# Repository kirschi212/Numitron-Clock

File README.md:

# Numitron Clock by Kirschi

This is a small documentation if you want to build a Numitron Clock by yourself. This project is build around IV-9 tubes, an ESP8266 and the MAX7315 IO-Expander.

## Images

## Functioning

The ESP8266 is connected to the WiFi and retrieves the current time from a time server. The MAX7315 IO expanders are then controlled by the ESP8266 via I2C and switch the corresponding segments of the Numitron segments.
Optionally, a switch can also be installed with which the tubes can be switched off.

------

## Parts list

### Main Components:

Component  | Quantity | Description |
------------- | ------------- | ------------- |
ESP8266 NodeMCU  | 1 | heart of the circuit |
IV-9 numitron tubes | 4 | retro 7 segment displays |
MAX7315AEE+ | 4 | 8-bit IO-Expanders |
Custom PCB | 1 | Eagle.CAD files are uploaded in this repository |

### Other Components:

| Component  | Quantity | Description |
| ------------- | ------------- | ------------- | 
| Resistor 0603 47Ω  | 32  | current limiting resistors for numitron segments |
| Resistor 0603 4.7kΩ  | 2  | pull-up resistors for I2C-Bus |
| Ceramic capacitors  0603 0.047µF  | 4  | decoupling capacitors for MAX7315 |
| USB-C panel jack  | 1  | used for power supply via USB-C |
                    
### Optional Components:
These components can optionally be installed.

| Component  | Quantity | Description |
| ------------- | ------------- | ------------- |
| Resistor 0603 10kΩ  | 1 | pull-up resistor for switch |
| Electrolytic capacitor 100µF   | 1  | capacitor for voltage stabilization |
| Mechanical switch  | 1  | used for turning all segments on or off |

##### Notice: Either the electrolytic capacitor OR switch can be installed with this version of the PCB-design.

## PCB: schematic and board

#### Notice: This current version of the PCB shows some minor mistakes, e.g. the electrolytic capacitor can only be placed without installing a switch. Nevertheless the board is fully functional! If you are interested, I could design a second version of this board and I will try to improve it!

## Casing

In the repository you can find the Fusion360 file to the casing that I designed myself. It features mounting holes for the PCB, cutouts for the USB-C panel jack and the switch. You can print it with a common 3D-printer using PLA or PETG.

------
## Code

The code was designed to be uploaded to the ESP8266 via the Arduino IDE and a USB-connection.

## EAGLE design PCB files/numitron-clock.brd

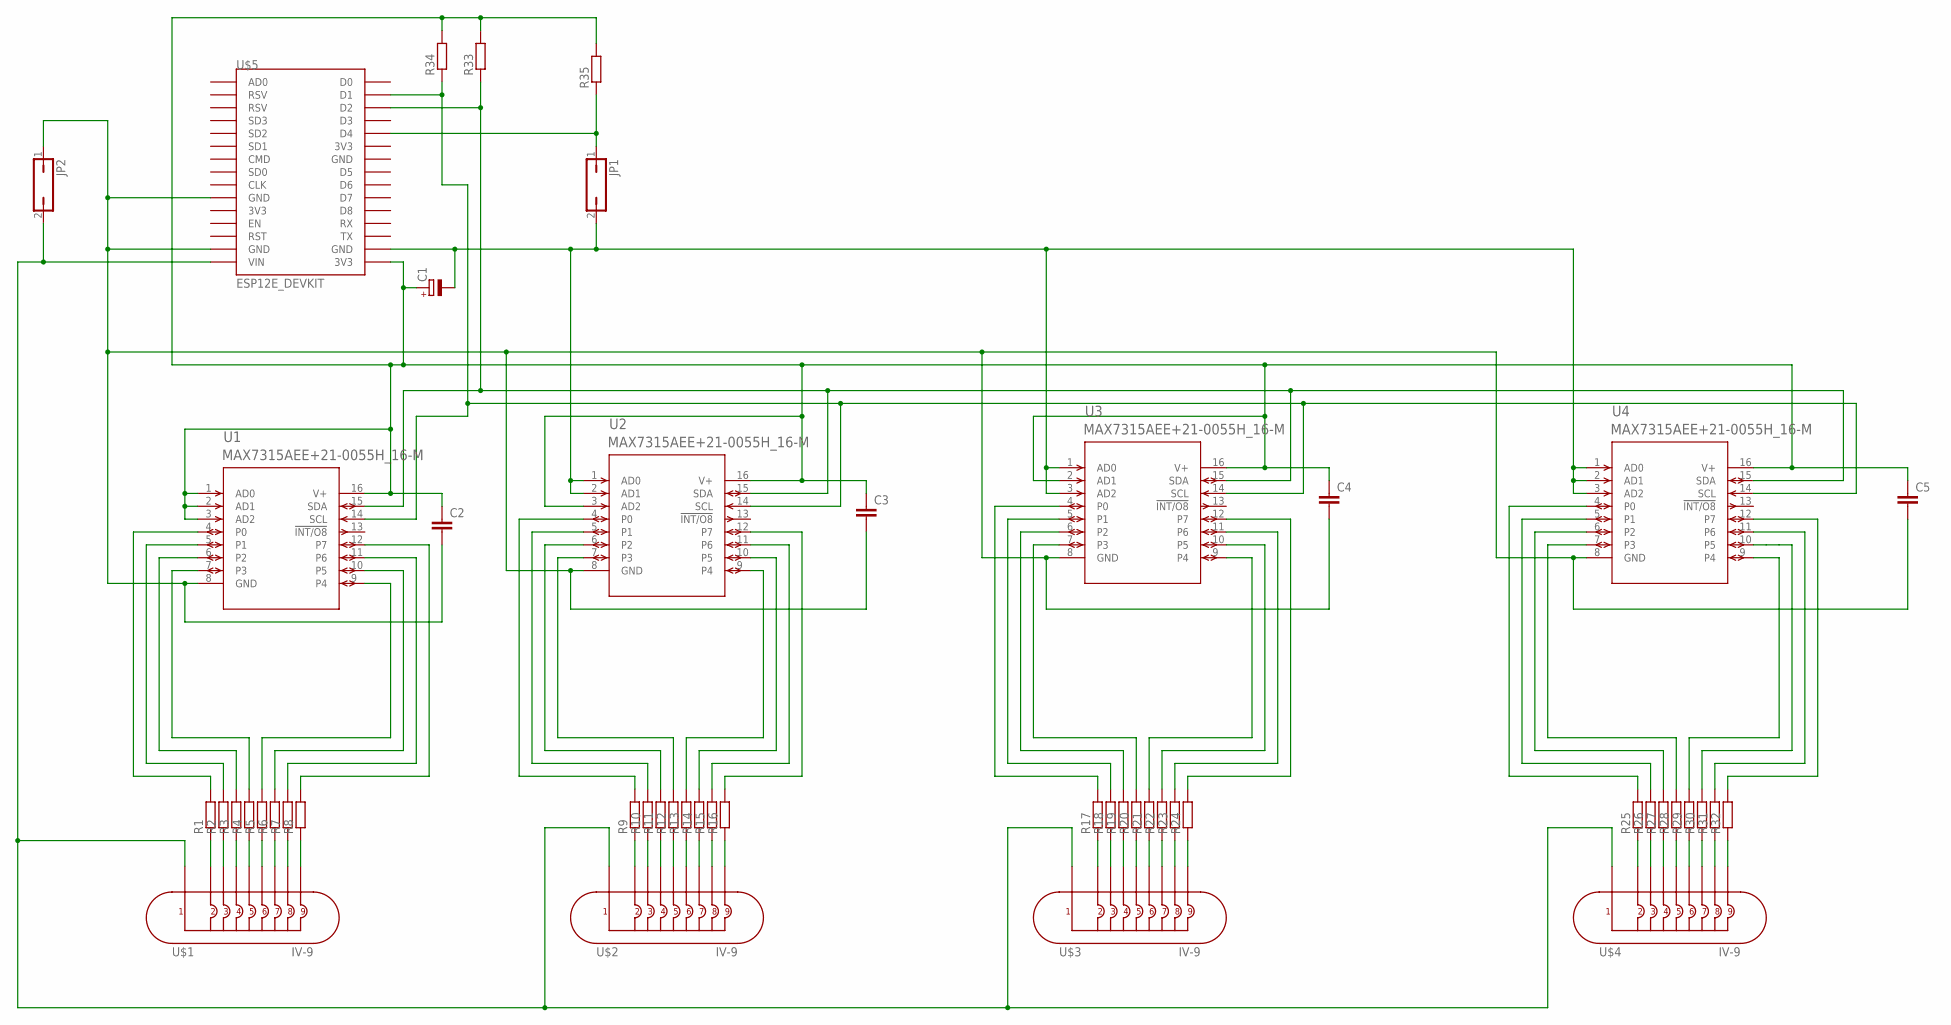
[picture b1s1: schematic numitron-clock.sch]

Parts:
C1: CPOL-EUE2,5-6E; E2,5-6E
C2, C3, C4, C5: C-EUC0603; C0603
JP1, JP2: JP1Q; JP1
R1, R2, R3, R4, R5, R6, R7, R8, R9, R10, R11, R12, R13, R14, R15, R16, R17, R18, R19, R20, R21, R22, R23, R24, R25, R26, R27, R28, R29, R30, R31, R32, R33, R34, R35: R-EU_R0603; R0603
U1, U2, U3, U4: MAX7315AEE+21-0055H_16-M; 21-0055H_16-M
U$1, U$2, U$3, U$4: IV-9
U$5: ESP12E_DEVKIT

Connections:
unnamed: R1.1, U$1.2
unnamed: R2.1, U$1.3
unnamed: R3.1, U$1.4
unnamed: R4.1, U$1.5
unnamed: R5.1, U$1.6
unnamed: R6.1, U$1.7
unnamed: R7.1, U$1.8
unnamed: R8.1, U$1.9
unnamed: R1.2, U1.4 (P0)
unnamed: R33.1, U1.15 (SDA), U2.15 (SDA), U3.15 (SDA), U4.15 (SDA), U$5.D2
unnamed: R34.1, U1.14 (SCL), U2.14 (SCL), U3.14 (SCL), U4.14 (SCL), U$5.D1
unnamed: R2.2, U1.5 (P1)
unnamed: JP2.2, U$1.1, U$2.1, U$3.1, U$4.1, U$5.VIN
unnamed: R3.2, U1.6 (P2)
unnamed: R4.2, U1.7 (P3)
unnamed: R5.2, U1.9 (P4)
unnamed: C1.+, C2.1, C3.1, C4.1, C5.1, R33.2, R34.2, R35.2, U1.1 (AD0), U1.2 (AD1), U1.3 (AD2), U1.16 (V+), U2.3 (AD2), U2.16 (V+), U3.2 (AD1), U3.16 (V+), U4.16 (V+), U$5.3V3@2 (3V3)
unnamed: R6.2, U1.10 (P5)
unnamed: R7.2, U1.11 (P6)
unnamed: R8.2, U1.12 (P7)
unnamed: R12.2, U2.7 (P3)
unnamed: R11.2, U2.6 (P2)
unnamed: R10.2, U2.5 (P1)
unnamed: R9.2, U2.4 (P0)
unnamed: R13.2, U2.9 (P4)
unnamed: R14.2, U2.10 (P5)
unnamed: R15.2, U2.11 (P6)
unnamed: R16.2, U2.12 (P7)
unnamed: R17.2, U3.4 (P0)
unnamed: R18.2, U3.5 (P1)
unnamed: R19.2, U3.6 (P2)
unnamed: R20.2, U3.7 (P3)
unnamed: R21.2, U3.9 (P4)
unnamed: R22.2, U3.10 (P5)
unnamed: R23.2, U3.11 (P6)
unnamed: R24.2, U3.12 (P7)
unnamed: R25.2, U4.4 (P0)
unnamed: R26.2, U4.5 (P1)
unnamed: R27.2, U4.6 (P2)
unnamed: R28.2, U4.7 (P3)
unnamed: R29.2, U4.9 (P4)
unnamed: R30.2, U4.10 (P5)
unnamed: R31.2, U4.11 (P6)
unnamed: R32.2, U4.12 (P7)
unnamed: JP1.1, R35.1, U$5.D4
unnamed: C2.2, C3.2, C4.2, C5.2, JP2.1, U1.8 (GND), U2.8 (GND), U3.8 (GND), U4.8 (GND), U$5.GND@0 (GND), U$5.GND@1 (GND)
unnamed: C1.-, JP1.2, U2.1 (AD0), U2.2 (AD1), U3.1 (AD0), U3.3 (AD2), U4.1 (AD0), U4.2 (AD1), U4.3 (AD2), U$5.GND@3 (GND)
unnamed: R25.1, U$4.2
unnamed: R26.1, U$4.3
unnamed: R27.1, U$4.4
unnamed: R28.1, U$4.5
unnamed: R29.1, U$4.6
unnamed: R30.1, U$4.7
unnamed: R31.1, U$4.8
unnamed: R32.1, U$4.9
unnamed: R17.1, U$3.2
unnamed: R18.1, U$3.3
unnamed: R19.1, U$3.4
unnamed: R20.1, U$3.5
unnamed: R21.1, U$3.6
unnamed: R22.1, U$3.7
unnamed: R23.1, U$3.8
unnamed: R24.1, U$3.9
unnamed: R9.1, U$2.2
unnamed: R10.1, U$2.3
unnamed: R11.1, U$2.4
unnamed: R12.1, U$2.5
unnamed: R13.1, U$2.6
unnamed: R14.1, U$2.7
unnamed: R15.1, U$2.8
unnamed: R16.1, U$2.9

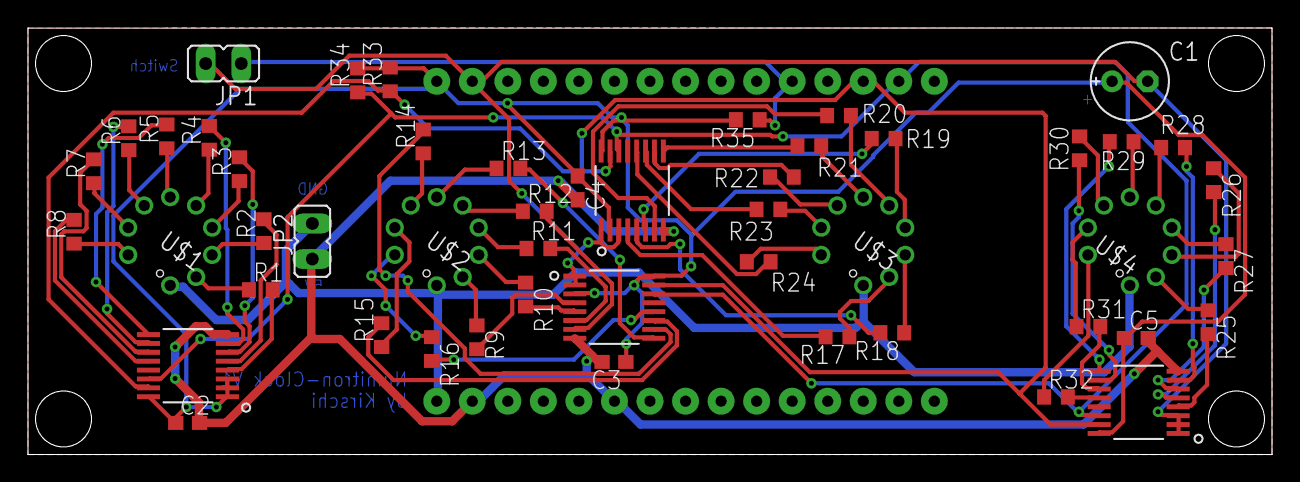
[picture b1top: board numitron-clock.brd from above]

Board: 2 copper layers, 88.9 x 30.5 mm, 51 parts (1 on the bottom side), 71 nets.

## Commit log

2024-07-08 Added PCB files
2024-07-08 Added code
2024-07-08 Added files for casing
2024-07-09 Added documentation

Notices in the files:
parts and their libraries:
COPYRIGHT: Copyright (C) 2024 Ultra Librarian. All rights reserved.
